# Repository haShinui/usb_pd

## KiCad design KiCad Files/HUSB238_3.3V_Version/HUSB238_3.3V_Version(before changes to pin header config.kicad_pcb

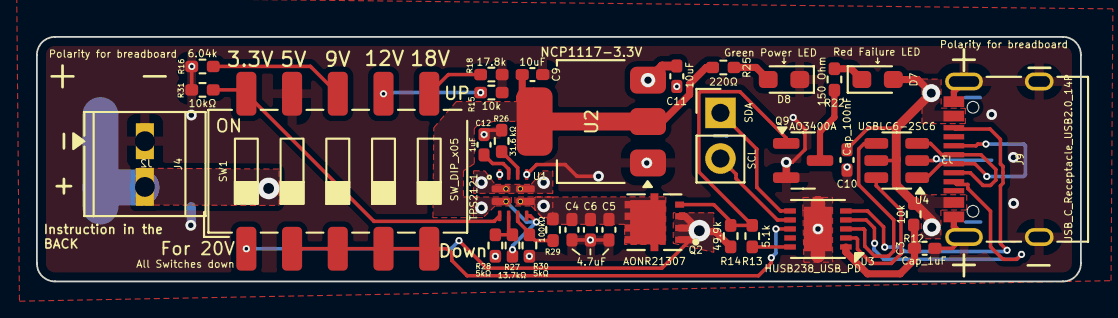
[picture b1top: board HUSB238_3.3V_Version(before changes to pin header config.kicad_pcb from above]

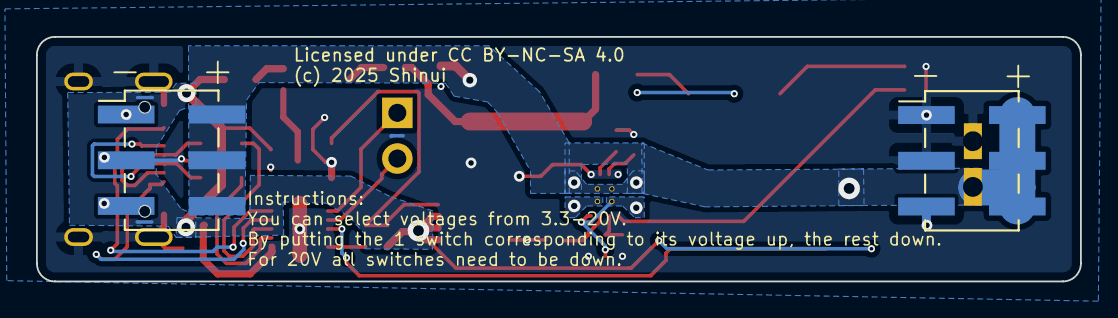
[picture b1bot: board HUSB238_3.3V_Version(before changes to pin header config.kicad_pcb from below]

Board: 2 copper layers, 58.0 x 13.6 mm, 36 parts (2 on the bottom side), 28 nets.

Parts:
C3: Cap_1uF; C_0402_1005Metric_Pad0.74x0.62mm_HandSolder
C4, C6: Cap_4.7uF; C_0402_1005Metric_Pad0.74x0.62mm_HandSolder
C5: 4.7uF; C_0402_1005Metric_Pad0.74x0.62mm_HandSolder
C9, C11: 10uF; C_0402_1005Metric_Pad0.74x0.62mm_HandSolder
C10: Cap_100nF; C_0402_1005Metric_Pad0.74x0.62mm_HandSolder
C12: 1uF; C_0402_1005Metric_Pad0.74x0.62mm_HandSolder
D7: Red Failure LED; LED_0603_1608Metric_Pad1.05x0.95mm_HandSolder
D8: Green Power LED; LED_0603_1608Metric_Pad1.05x0.95mm_HandSolder
J2, J3: Conn_02x02_Counter_Clockwise; PinHeader_2x03_P2.54mm_Vertical_SMD
J4: Conn_01x02_Pin; TerminalBlock_TE_282834-2_1x02_P2.54mm_Horizontal
J9: USB_C_Receptacle_USB2.0_14P; USB_C_Receptacle_XKB_U262-16XN-4BVC11
N21: Conn_01x02_Pin; PinHeader_1x02_P2.54mm_Vertical
Q2: AONR21307; TRANS_AONR21307
Q9: AO3400A; SOT-23
R12, R15: 10k; R_0402_1005Metric_Pad0.72x0.64mm_HandSolder
R13: 5.1k; R_0402_1005Metric_Pad0.72x0.64mm_HandSolder
R14: 49.9k; R_0402_1005Metric_Pad0.72x0.64mm_HandSolder
R16: 6.04k; R_0402_1005Metric_Pad0.72x0.64mm_HandSolder
R18: 17.8k; R_0402_1005Metric_Pad0.72x0.64mm_HandSolder
R22: 150 Ohm; R_0402_1005Metric_Pad0.72x0.64mm_HandSolder
R25: 220Ω; R_0402_1005Metric_Pad0.72x0.64mm_HandSolder
R26: 31.6 kΩ; R_0402_1005Metric_Pad0.72x0.64mm_HandSolder
R27: 13.7kΩ; R_0402_1005Metric_Pad0.72x0.64mm_HandSolder
R28, R30: 5kΩ; R_0402_1005Metric_Pad0.72x0.64mm_HandSolder
R29: 100kΩ; R_0402_1005Metric_Pad0.72x0.64mm_HandSolder
R31: 10kΩ; R_0402_1005Metric_Pad0.72x0.64mm_HandSolder
SW1: SW_DIP_x05; SW_DIP_SPSTx05_Slide_6.7x14.26mm_W8.61mm_P2.54mm_LowProfile
U1: TPS2121; IC_TPS2121RUXR
U2: NCP1117-3.3V; SOT-223-3_TabPin2
U3: HUSB238_USB_PD; DFN-10-1EP_3x3mm_P0.5mm_EP1.55x2.48mm
U4: USBLC6-2SC6; SOT-23-6

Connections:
+3.3V: C9.1, R25.2, R27.2, U1.2 (IN2), U1.6 (PR1), U2.2 (VO)
/SET: R31.1, SW1.10, U1.3 (CP2)
/USB_M: U3.3 (D-), U4.4 (I/O2)
/USB_P: U3.2 (D+), U4.6 (I/O1)
/VBUS: C10.2, D7.2 (A), J9.A4 (VBUS), J9.A9 (VBUS), J9.B4 (VBUS), J9.B9 (VBUS), Q2.1, Q2.2, Q2.3, R12.2, R14.2, SW1.1, U4.5 (VBUS)
GND: C3.1, C4.1, C5.1, C6.1, C9.2, C10.1, C11.2, C12.1, D8.1 (K), J2.1, J2.3, J2.5, J3.1, J3.3, J3.5, J4.1, J9.A1 (GND), J9.A12 (GND), J9.B1 (GND), J9.B12 (GND), J9.S1 (SHIELD), Q9.2 (S), R15.1, R16.1, R18.1, R26.2, R28.1, R30.1, R31.2, SW1.9, U1.9 (ST), U1.12 (GND), U2.1 (GND), U3.11 (GND), U4.2 (GND)
unnamed: D7.1 (K), R22.1
unnamed: D8.2 (A), R25.1
unnamed: J9.A5 (CC1), U3.4 (CC1)
unnamed: J9.B5 (CC2), U3.5 (CC2)
unnamed: J9.A6 (D+), J9.B6 (D+), U4.1 (I/O1)
unnamed: J9.A7 (D-), J9.B7 (D-), U4.3 (I/O2)
unnamed: Q9.3 (D), R22.2
unnamed: Q2.4, Q9.1 (G), R13.2, R14.1
unnamed: R15.2, SW1.7
unnamed: R16.2, SW1.8
unnamed: R18.2, SW1.6
unnamed: R26.1, U1.10 (ILIM)
unnamed: R29.1, R30.2, U1.5 (OV1)
unnamed: R27.1, R28.2, U1.4 (OV2)
unnamed: C12.2, U1.11 (SS)
unnamed: R13.1, U3.10 (Gate)
unnamed: C3.2, R12.1, U3.1 (VIN)
unnamed: SW1.2, SW1.3, SW1.4, SW1.5, U3.8 (VSET)
SCL 1: N21.2, U3.7 (SCL)
SDA 1: N21.1, U3.6 (SDA)
VCC: C11.1, J2.2, J2.4, J2.6, J3.2, J3.4, J3.6, J4.2, U1.1 (OUT), U1.8 (OUT), U2.3 (VI)
VDD: C4.2, C5.2, C6.2, Q2.5_6_7_8, R29.2, U1.7 (IN1)

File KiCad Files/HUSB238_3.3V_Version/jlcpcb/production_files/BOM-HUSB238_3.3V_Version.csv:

Comment,Designator,Footprint,LCSC,Quantity
17.8kΩ,R18,R_0402_1005Metric_Pad0.72x0.64mm_HandSolder,C129766,1
10uF,"C11,C9",C_0402_1005Metric_Pad0.74x0.62mm_HandSolder,C194427,2
Green Power LED,D8,LED_0603_1608Metric_Pad1.05x0.95mm_HandSolder,C205450,1
AO3400A,Q9,SOT-23,C20917,1
150Ω,R22,R_0402_1005Metric_Pad0.72x0.64mm_HandSolder,C25082,1
220Ω,R25,R_0402_1005Metric_Pad0.72x0.64mm_HandSolder,C25091,1
100kΩ,R29,R_0402_1005Metric_Pad0.72x0.64mm_HandSolder,C25741,1
10kΩ,"R12,R15,R31",R_0402_1005Metric_Pad0.72x0.64mm_HandSolder,C25744,3
13.7kΩ,R27,R_0402_1005Metric_Pad0.72x0.64mm_HandSolder,C25854,1
49.9kΩ,R14,R_0402_1005Metric_Pad0.72x0.64mm_HandSolder,C25897,1
5.1kΩ,R13,R_0402_1005Metric_Pad0.72x0.64mm_HandSolder,C25905,1
NCP1117-3.3_SOT223,U2,SOT-223-3_TabPin2,C26537,1
USB_C_Receptacle_USB2.0_14P,J9,USB_C_Receptacle_XKB_U262-16XN-4BVC11,C2988369,1
31.6 kΩ,R26,R_0402_1005Metric_Pad0.72x0.64mm_HandSolder,C2998091,1
1uF,"C12,C3,C4,C5,C6",C_0402_1005Metric_Pad0.74x0.62mm_HandSolder,C307413,5
100nF,C10,C_0402_1005Metric_Pad0.74x0.62mm_HandSolder,C343047,1
AONR21357,Q2,TRANS_AONR21307,C431196,1
TPS2121,U1,IC_TPS2121RUXR,C485916,1
USBLC6,U4,SOT-23-6,C5180249,1
5kΩ,"R28,R30",R_0402_1005Metric_Pad0.72x0.64mm_HandSolder,C5948099,2
SW_DIP_x05,SW1,SW_DIP_SPSTx05_Slide_6.7x14.26mm_W8.61mm_P2.54mm_LowProfile,C7471375,1
HUSB238_USB_PD,U3,DFN-10-1EP_3x3mm_P0.5mm_EP1.55x2.48mm,C7471904,1
Red Failure LED,D7,LED_0603_1608Metric_Pad1.05x0.95mm_HandSolder,C965799,1
6.04kΩ,R16,R_0402_1005Metric_Pad0.72x0.64mm_HandSolder,C97819,1

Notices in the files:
KiCad Files/HUSB238_3.3V_Version/HUSB238_3.3V_Version(before changes to pin header config.kicad_pcb:
Licensed under CC BY-NC-SA 4.0
(c) 2025 Shinui
